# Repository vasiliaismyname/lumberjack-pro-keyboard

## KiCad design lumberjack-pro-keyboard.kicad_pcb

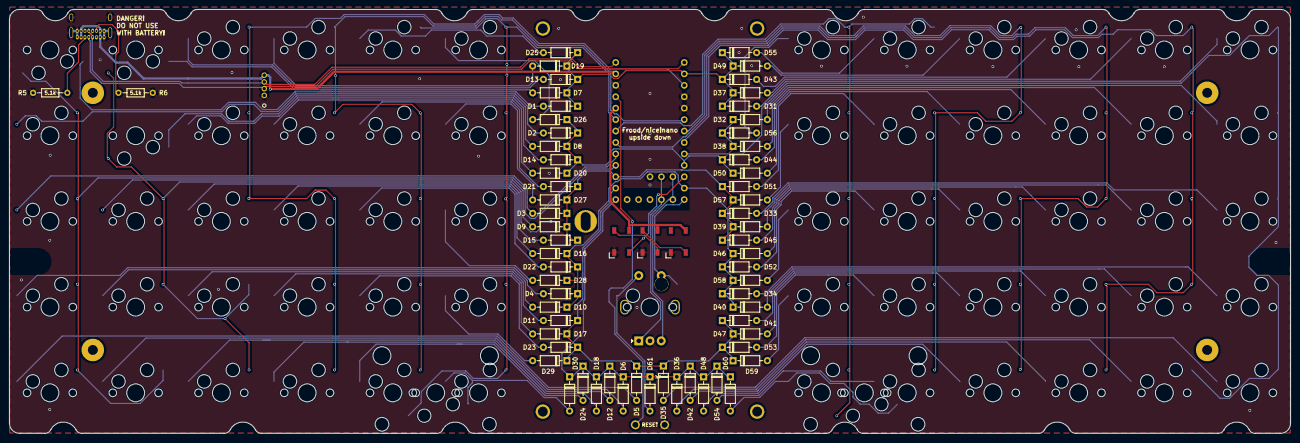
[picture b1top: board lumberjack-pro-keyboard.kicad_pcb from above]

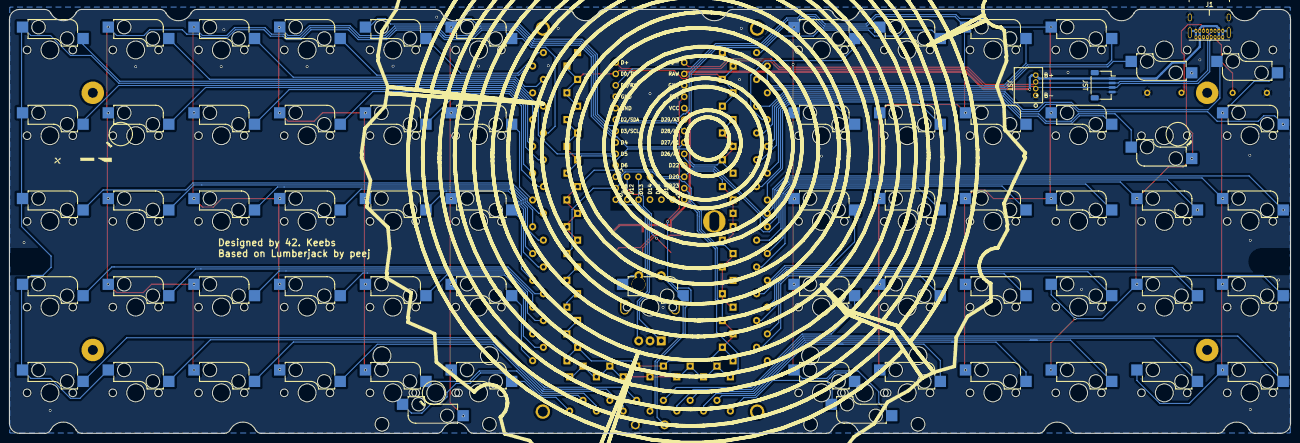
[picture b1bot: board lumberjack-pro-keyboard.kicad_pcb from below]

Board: 2 copper layers, 284.7 x 94.2 mm, 149 parts (6 on the bottom side), 91 nets.

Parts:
2u_MX30, 2u_MX60: SW_Push; Kailh_MX_Socket-2u-swapped-pads-reversed-stabilizer-rotated
D1, D2, D3, D4, D5, D6, D7, D8, D9, D10, D11, D12, D13, D14, D15, D16, D17, D18, D19, D20, D21, D22, D23, D24, D25, D26, D27, D28, D29, D30, D31, D32, D33, D34, D35, D36, D37, D38, D39, D40, D41, D42, D43, D44, D45, D46, D47, D48, D49, D50, D51, D52, D53, D54, D55, D56, D57, D58, D59, D60, D61: 1N4148; D_DO-35_SOD27_P7.62mm_Horizontal
H1, H2, H3, H4: M2; MountingHole_M2_3.2_mm
H5, H6, H7: M2; MountingSlot_M2
H8, H9, H10, H11: M2; MountingHole_M2
J1: USB; USB_C_GCT_USB4085-offset-pads
J3: JST; JST_SH_SM04B-SRSS-TB_1x04-1MP_P1.00mm_Horizontal
J4: JST; S4B-ZRLFSN
LOGO1: OSHW Logo; OSHW
LOGO2: Lumberjack Pro; Lumberjack-Pro-Frood
LOGO3: Flags; Flags-NL-CZ-EU
MX1, MX2, MX3, MX4, MX5, MX6, MX7, MX8, MX9, MX10, MX11, MX12, MX13, MX14, MX15, MX16, MX17, MX18, MX19, MX20, MX21, MX22, MX23, MX24, MX25, MX26, MX27, MX28, MX29, MX30, MX31, MX32, MX33, MX34, MX35, MX36, MX37, MX38, MX39, MX40, MX41, MX42, MX43, MX44, MX45, MX46, MX47, MX48, MX49, MX50, MX51, MX52, MX53, MX54, MX55, MX56, MX57, MX58, MX59, MX60: SW_Push; Kailh_MX_Socket-swapped-pads-with-cutout
MX61: SW_Push+EC11; Kailh_MX_Socket-swapped-pads+EC11_with_cutouts
R5, R6: 5.1k; R_Axial_DIN0204_L3.6mm_D1.6mm_P7.62mm_Horizontal
RGB1, RGB2, RGB3: WS2812B; LED_WS2812B_PLCC4_5.0x5.0mm_P3.2mm
SILK1: Silkscreen Wood Graphics; wood
SW1: RESET; TACT_SWITCH_TVBP06_single
U1: Frood/nice!nano; Frood-nice_nano_PinHeader_2x13+5_P2.54mm_upside_down

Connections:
+3V3: RGB1.1 (VDD), RGB2.1 (VDD), RGB3.1 (VDD), U1.27 (VCC)
/COL0: MX1.2, MX2.2, MX3.2, MX4.2, MX5.2, MX6.2, U1.23 (GPIO26)
/COL1: MX7.2, MX8.2, MX9.2, MX10.2, MX11.2, MX12.2, U1.22 (GPIO22)
/COL2: MX13.2, MX14.2, MX15.2, MX16.2, MX17.2, MX18.2, U1.3 (GPIO1)
/COL3: MX19.2, MX20.2, MX21.2, MX22.2, MX23.2, MX24.2, U1.6 (GPIO2)
/COL4: 2u_MX30.2, MX25.2, MX26.2, MX27.2, MX28.2, MX29.2, MX30.2, U1.26 (GPIO29)
/COL5: MX31.2, MX32.2, MX33.2, MX34.2, MX35.2, MX36.2, U1.9 (GPIO5)
/COL6: MX37.2, MX38.2, MX39.2, MX40.2, MX41.2, MX42.2, U1.8 (GPIO4)
/COL7: MX43.2, MX44.2, MX45.2, MX46.2, MX47.2, MX48.2, U1.24 (GPIO27)
/COL8: MX49.2, MX50.2, MX51.2, MX52.2, MX53.2, MX54.2, U1.7 (GPIO3)
/COL9: 2u_MX60.2, MX55.2, MX56.2, MX57.2, MX58.2, MX59.2, MX60.2, U1.25 (GPIO28)
/COL10: MX61.2, MX61.S2, U1.13 (GPIO9)
/EN_A: MX61.A, U1.15 (GPIO13), U1.33 (P1.02)
/EN_B: MX61.B, U1.14 (GPIO12), U1.32 (P1.07)
/RESET: SW1.1, U1.28 (RST)
/RGB: RGB1.4 (DIN), U1.11 (GPIO7)
/ROW0: D1.1 (K), D7.1 (K), D13.1 (K), D19.1 (K), D25.1 (K), D31.1 (K), D37.1 (K), D43.1 (K), D49.1 (K), D55.1 (K), U1.2 (GPIO0)
/ROW1: D2.1 (K), D8.1 (K), D14.1 (K), D20.1 (K), D26.1 (K), D32.1 (K), D38.1 (K), D44.1 (K), D50.1 (K), D56.1 (K), U1.10 (GPIO6)
/ROW2: D3.1 (K), D9.1 (K), D15.1 (K), D21.1 (K), D27.1 (K), D33.1 (K), D39.1 (K), D45.1 (K), D51.1 (K), D57.1 (K), U1.21 (GPIO20)
/ROW3: D4.1 (K), D10.1 (K), D16.1 (K), D22.1 (K), D28.1 (K), D34.1 (K), D40.1 (K), D46.1 (K), D52.1 (K), D58.1 (K), U1.12 (GPIO8)
/ROW4: D5.1 (K), D11.1 (K), D17.1 (K), D23.1 (K), D29.1 (K), D35.1 (K), D41.1 (K), D47.1 (K), D53.1 (K), D59.1 (K), U1.20 (GPIO23)
/ROW5: D6.1 (K), D12.1 (K), D18.1 (K), D24.1 (K), D30.1 (K), D36.1 (K), D42.1 (K), D48.1 (K), D54.1 (K), D60.1 (K), D61.1 (K), U1.19 (GPIO21)
/USB_D+: J1.A6 (D+), J1.B6 (D+), J3.3, J4.2, U1.1 (USB_D+)
/USB_D-: J1.A7 (D-), J1.B7 (D-), J3.2, J4.3, U1.31 (USB_D-)
GND: J1.A1 (GND), J1.A12 (GND), J1.B1 (GND), J1.B12 (GND), J1.S1 (SHIELD), J3.4, J4.1, MX61.C, R5.1, R6.1, RGB1.3 (VSS), RGB2.3 (VSS), RGB3.3 (VSS), SW1.2, U1.4 (GND), U1.5 (GND), U1.29 (GND)
unnamed: D1.2 (A), MX1.1
unnamed: D2.2 (A), MX2.1
unnamed: D3.2 (A), MX3.1
unnamed: D4.2 (A), MX4.1
unnamed: D5.2 (A), MX5.1
unnamed: D6.2 (A), MX6.1
unnamed: D7.2 (A), MX7.1
unnamed: D8.2 (A), MX8.1
unnamed: D9.2 (A), MX9.1
unnamed: D10.2 (A), MX10.1
unnamed: D11.2 (A), MX11.1
unnamed: D12.2 (A), MX12.1
unnamed: D13.2 (A), MX13.1
unnamed: D14.2 (A), MX14.1
unnamed: D15.2 (A), MX15.1
unnamed: D16.2 (A), MX16.1
unnamed: D17.2 (A), MX17.1
unnamed: D18.2 (A), MX18.1
unnamed: D19.2 (A), MX19.1
unnamed: D20.2 (A), MX20.1
unnamed: D21.2 (A), MX21.1
unnamed: D22.2 (A), MX22.1
unnamed: D23.2 (A), MX23.1
unnamed: D24.2 (A), MX24.1
unnamed: D25.2 (A), MX25.1
unnamed: D26.2 (A), MX26.1
unnamed: D27.2 (A), MX27.1
unnamed: D28.2 (A), MX28.1
unnamed: D29.2 (A), MX29.1
unnamed: 2u_MX30.1, D30.2 (A), MX30.1
unnamed: D31.2 (A), MX31.1
unnamed: D32.2 (A), MX32.1
unnamed: D33.2 (A), MX33.1
unnamed: D34.2 (A), MX34.1
unnamed: D35.2 (A), MX35.1
unnamed: D36.2 (A), MX36.1
unnamed: D37.2 (A), MX37.1
unnamed: D38.2 (A), MX38.1
unnamed: D39.2 (A), MX39.1
unnamed: D40.2 (A), MX40.1
unnamed: D41.2 (A), MX41.1
unnamed: D42.2 (A), MX42.1
unnamed: D43.2 (A), MX43.1
unnamed: D44.2 (A), MX44.1
unnamed: D45.2 (A), MX45.1
unnamed: D46.2 (A), MX46.1
unnamed: D47.2 (A), MX47.1
unnamed: D48.2 (A), MX48.1
unnamed: D49.2 (A), MX49.1
unnamed: D50.2 (A), MX50.1
unnamed: D51.2 (A), MX51.1
unnamed: D52.2 (A), MX52.1
unnamed: D53.2 (A), MX53.1
unnamed: D54.2 (A), MX54.1
unnamed: D55.2 (A), MX55.1
unnamed: D56.2 (A), MX56.1
unnamed: D57.2 (A), MX57.1
unnamed: D58.2 (A), MX58.1
unnamed: D59.2 (A), MX59.1
unnamed: 2u_MX60.1, D60.2 (A), MX60.1
unnamed: D61.2 (A), MX61.1, MX61.S1
unnamed: J1.A5 (CC1), R5.2
unnamed: J1.B5 (CC2), R6.2
unnamed: RGB1.2 (DOUT), RGB2.4 (DIN)
unnamed: RGB2.2 (DOUT), RGB3.4 (DIN)
VBUS: J1.A4 (VBUS), J1.A9 (VBUS), J1.B4 (VBUS), J1.B9 (VBUS), J3.1, J4.4, U1.30 (RAW)

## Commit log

2026-01-22 Update silkscreen
2026-05-30 Add GitHub Action for generating gerber files
2026-05-30 Add workflow_dispatch trigger and yml path filter to PR trigger
2026-05-30 Install zip utility before packaging gerbers
2026-05-30 Run apt-get update before installing zip
2026-05-30 Add GitHub Action for generating gerber files (#2)
    * Add GitHub Action for generating gerber files
    * Add workflow_dispatch trigger and yml path filter to PR trigger
    * Install zip utility before packaging gerbers
    * Run apt-get update before installing zip

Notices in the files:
parts and their libraries:
Copyright 2021 Accelerated Designs. All rights reserved.
